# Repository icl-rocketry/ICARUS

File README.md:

# ICARUS
Imperial College london rocketry Attempts to be Resourceful by Using Solar power. A CanSat for the Mach-22 Competition

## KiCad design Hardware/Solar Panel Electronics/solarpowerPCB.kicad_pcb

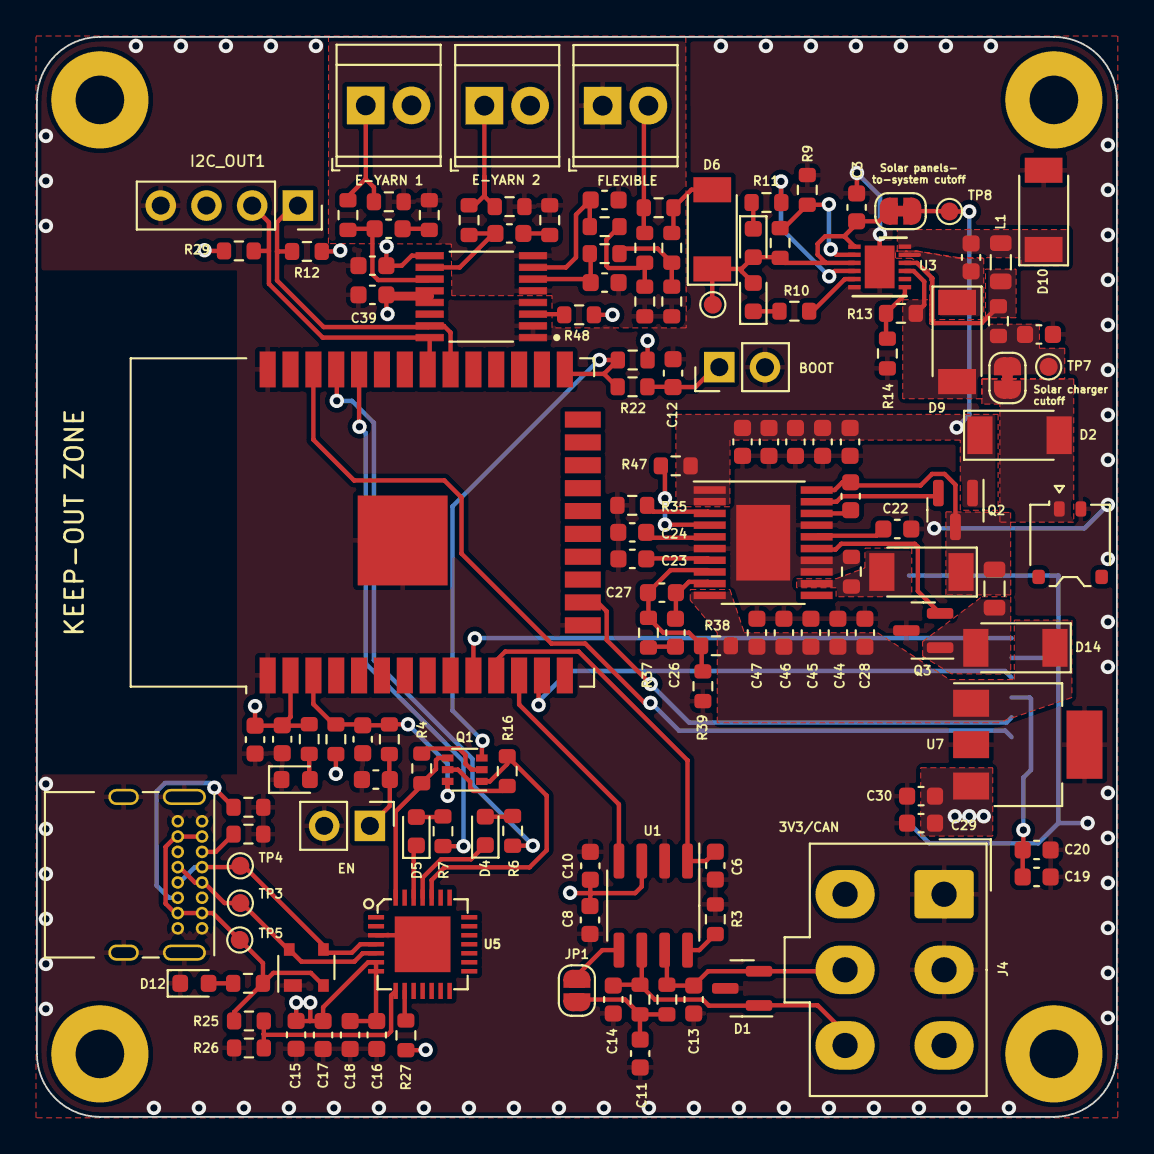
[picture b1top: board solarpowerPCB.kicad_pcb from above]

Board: 2 copper layers, 60.0 x 60.0 mm, 136 parts (1 on the bottom side), 80 nets.

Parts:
C1, C10, C20, C28, C29, C39: 10uF; C_0603_1608Metric
C2, C11, C12, C17, C18, C19, C38: 0.1uF; C_0603_1608Metric
C3, C5: 10u; C_0603_1608Metric
C4, C22: 1u; C_0603_1608Metric
C6: 160pF; C_0603_1608Metric
C7, C9: 1uF; C_0603_1608Metric
C8, C30: 100nF; C_0603_1608Metric
C13: 220pF; C_0603_1608Metric
C14: 220 pF; C_0603_1608Metric
C15: 47uF; C_0603_1608Metric
C16: 1.0uF; C_0603_1608Metric
C21, C40, C41, C42, C43: 2.2u; C_0603_1608Metric
C23, C25: 0.1u; C_0603_1608Metric
C24: 1.6n; C_0603_1608Metric
C26: 55nF; C_0603_1608Metric
C27: 0.01nF; C_0603_1608Metric
C31, C32: 10nF; C_0603_1608Metric
C33, C34: C_0603_1608Metric
C44, C45: 47u; C_0603_1608Metric
C46, C47: 0.47u; C_0603_1608Metric
D1: SM712_SOT23; SOT-23
D2, D10: CMSH3-20MA; D_SOD-128
D3, D4, D5: LED; LED_0603_1608Metric
D6: CMSH1-20MA; D_SOD-128
D7: FAULT LED; LED_0603_1608Metric
D8: CHRG LED; LED_0603_1608Metric
D9: D; D_SOD-128
D11: SP0503BAHT; SOT-143
D12: USB_LED; LED_0603_1608Metric
D13: D_Schottky_10V_1.5A; D_SOD-128
D14: D_Schottky_6V; D_SOD-128
I2C_OUT1: Conn_01x04_Female; PinSocket_1x04_P2.54mm_Vertical
J1: Screw_Terminal_SolarPanel_Input; TerminalBlock_TE_282834-2_1x02_P2.54mm_Horizontal
J3, J5: Conn_01x02_Male; PinHeader_1x02_P2.54mm_Vertical
J4: Conn_01x06_Male; Molex_Mini-Fit_Jr_5566-06A_2x03_P4.20mm_Vertical
J6: USB_C_Receptacle_USB2.0; USB_C_Receptacle_GCT_USB4085
J7: microSD_HC_Wuerth_693072010801
J13: Battery Connector; JST_ACH_BM02B-ACHSS-GAN-ETF_1x02-1MP_P1.20mm_Vertical
JP1: SolderJumper_2_Open; SolderJumper-2_P1.3mm_Open_RoundedPad1.0x1.5mm
JP2, JP3: SolderJumper_2_Bridged; SolderJumper-2_P1.3mm_Bridged_RoundedPad1.0x1.5mm
L1: 10u; L_0805_2012Metric
L2: 17uH; L_0805_2012Metric
Patch1, Patch2: TerminalBlock_TE_282834-2_1x02_P2.54mm_Horizontal
Q1: MMDT2222A; SOT-363_SC-70-6
Q2, Q3: Q_NMOS_DGS; SOT-23
R3, R10, R11, R48: 10k; R_0603_1608Metric
R4, R16, R17, R19: 10K; R_0603_1608Metric
R5, R6, R7, R28: 470; R_0603_1608Metric
R8: 340k; R_0603_1608Metric
R9: 100k; R_0603_1608Metric
R12, R27, R29: 4.7k; R_0603_1608Metric
R13: 560k; R_0603_1608Metric
R14: 450k; R_0603_1608Metric
R15: 0.05; R_0603_1608Metric
R18, R22: 0; R_0603_1608Metric
R20, R21: 60; R_0603_1608Metric
R23, R24: 5.1k; R_0603_1608Metric
R25: 24k; R_0603_1608Metric
R26: 47k; R_0603_1608Metric
R30, R33, R47: 1M; R_0603_1608Metric
R31, R34: 400k; R_0603_1608Metric
R32: 0.22-Current Sense; R_0603_1608Metric
R35: 18.3k; R_0603_1608Metric
R36: 15m; R_0603_1608Metric
R37: 17k; R_0603_1608Metric
R38: 1000; R_0603_1608Metric
R39: 332; R_0603_1608Metric
R40, R41, R42, R43, R44, R45: 1k; R_0603_1608Metric
R_Shunt1, R_Shunt2: 1k; R_0603_1608Metric
TP3, TP4, TP5: TestPoint; TestPoint_Pad_D1.0mm
TP6: TP_Vsolarpanel; TestPoint_Pad_D1.0mm
TP7: TP_BAT; TestPoint_Pad_D1.0mm
TP8: TP_Vout; TestPoint_Pad_D1.0mm
U1: SN65HVD230; SOIC-8_3.9x4.9mm_P1.27mm
U2: ESP32-WROOM-32D; ESP32-WROOM-32
U3: LT3652EDD; DFN-12-1EP_3x3mm_P0.45mm_EP1.66x2.38mm
U5: CP2102-GMR-QFN28; QFN28G_0.5-5X5MM
U6: LM5118MH; Texas_PWP0020A
U7: LT1963AxST-3.3; SOT-223-3_TabPin2
U9: ADS1219IPWT; SOP65P640X120-16N

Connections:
+3V3: C1.1, C2.1, C8.1, C10.1, C15.2, C16.2, C17.2, C18.2, C19.1, C20.1, C29.2, C30.2, C38.1, C39.2, I2C_OUT1.3, J4.3, J7.4 (VDD), R5.1, R12.1, R17.1, R19.1, R27.1, R29.1, R48.2, U1.3 (VCC), U2.2 (VDD), U5.6 (VDD), U5.7 (REGIN), U7.3 (OUT), U9.9 (REFP), U9.12 (AVDD), U9.13 (DVDD)
/ADC/AIN0N: C31.2, R41.2
/ADC/AIN0P: C31.1, R40.1, U9.11 (AIN0)
/ADC/AIN1N: C32.2, R43.2
/ADC/AIN1P: C32.1, R42.1, U9.10 (AIN1)
/ADC/AIN2P: C33.1, R44.1, U9.7 (AIN2)
/ADC/AIN3P: C34.1, R45.1, U9.6 (AIN3)
/BOOT: Q1.3 (C2), R19.2, R22.1, U2.25 (IO0)
/CAN_HIGH: C13.2, D1.2 (A2), J4.5, R20.1, U1.7 (CANH)
/CAN_LOW: C14.2, D1.1 (A1), J4.6, R21.2, U1.6 (CANL)
/CAN_RX: U1.4 (R), U2.12 (IO27)
/CAN_TX: C6.2, U1.1 (D), U2.11 (IO26)
/DTR: Q1.4 (E2), R4.2, U5.28 (DTR)
/EN: C7.1, Q1.6 (C1), R17.2, R18.1, U2.3 (EN)
/HSPI_MISO: J7.7 (DAT0), U2.10 (IO25)
/HSPI_MOSI: J7.3 (CMD), U2.16 (IO13)
/HSPI_SCLK: J7.5 (CLK), U2.13 (IO14)
/RTS: Q1.1 (E1), R16.2, U5.24 (RTS)
/RXD: D4.1 (K), U5.25 (RXD)
/SCL: I2C_OUT1.2, R29.2, U2.31 (IO19), U9.16 (SCL)
/SDA: I2C_OUT1.1, R12.2, U2.30 (IO18), U9.15 (SDA)
/Solar Charger/V_solarpanel: J1.2, R30.1, R32.1
/SolarPanelVoltage1: R30.2, R31.1, R44.2
/SolarPanelVoltage2: R33.2, R34.1, R45.2
/TXD: D5.1 (K), U5.26 (TXD)
/VSolCharger: C21.1, C40.1, C41.1, C42.1, C43.1, D2.1 (K), JP2.2 (B), Q2.1 (D), R47.1, TP8.1, U6.1 (VIN), U6.2 (UVLO)
/VoltageReg/V_reg: C28.2, C44.1, C45.1, C46.1, C47.1, D14.1 (K), R38.1, U6.10 (VOUT), U7.1 (IN)
/Vref: JP1.1 (A), U1.5 (Vref)
/usb_to_uart/Data+: D11.3 (K), J6.A6 (D+), J6.B6 (D+), TP4.1, U5.4 (D+)
/usb_to_uart/Data-: D11.4 (K), J6.A7 (D-), J6.B7 (D-), TP3.1, U5.5 (D-)
/~SD_CS: J7.2 (DAT3/CD), U2.36 (IO22)
GND: C1.2, C2.2, C3.1, C5.1, C6.1, C7.2, C8.2, C9.1, C10.2, C11.2, C12.1, C13.1, C14.1, C15.1, C16.1, C17.1, C18.1, C19.2, C20.2, C21.2, C22.2, C23.2, C24.2, C28.1, C29.1, C30.1, C38.2, C39.1, C40.2, C41.2, C42.2, C43.2, C44.2, C45.2, C46.2, C47.2, D1.3 (common), D3.1 (K), D10.2 (A), D11.1 (A), D12.1 (K), I2C_OUT1.4, J3.2, J4.1, J4.2, J5.2, J6.A1 (GND), J6.A12 (GND), J6.B1 (GND), J6.B12 (GND), J6.S1 (SHIELD), J7.6 (VSS), J7.9 (SHIELD), J13.2, Q3.3 (S), R3.2, R9.2, R14.2, R23.2, R24.1, R26.1, R35.2, R36.2, R39.2, U1.2 (GND), U2.1 (GND), U2.15 (GND), U2.38 (GND), U2.39 (GND), U3.6 (TIMER), U3.13 (GND), U5.3 (GND), U5.29 (GND@1), U6.6 (AGND), U6.13 (CSG), U6.14 (PGND), U6.17 (VCCX), U6.21 (EP), U7.2 (GND), U9.1 (A0), U9.2 (A1), U9.4 (DGND)
GNDA: C33.2, C34.2, J1.1, Patch1.2, Patch2.2, R31.2, R34.2, R41.1, R43.1, R_Shunt1.2, R_Shunt2.2, U9.5 (AGND), U9.8 (REFN)
unnamed: C3.2, D6.1 (K), D7.2 (A), D8.2 (A), JP2.1 (A), R8.1, TP6.1, U3.1 (VIN), U3.3 (~SHDN)
unnamed: C4.1, D9.1 (K), U3.11 (BOOST)
unnamed: C4.2, D10.1 (K), L1.1, U3.12 (SW)
unnamed: C5.2, D9.2 (A), JP3.1 (A), R13.1, R15.2, TP7.1, U3.9 (BAT)
unnamed: C9.2, J3.1, R18.2
unnamed: C11.1, JP1.2 (B), R20.2, R21.1
unnamed: C12.2, J5.1, R22.2
unnamed: C22.1, U6.16 (VCC)
unnamed: C23.1, U6.7 (SS)
unnamed: C24.1, U6.5 (RAMP)
unnamed: C25.1, U6.18 (HB)
unnamed: C25.2, D13.1 (K), L2.1, Q2.3 (S), U6.20 (HS)
unnamed: C26.1, R37.1
unnamed: C26.2, C27.2, U6.9 (COMP)
unnamed: C27.1, R37.2, R38.2, R39.1, U6.8 (FB)
unnamed: D2.2 (A), J13.1, JP3.2 (B)
unnamed: D3.2 (A), R5.2
unnamed: D4.2 (A), R6.2
unnamed: D5.2 (A), R7.2
unnamed: D6.2 (A), R32.2, R33.1
unnamed: D7.1 (K), R10.1
unnamed: D8.1 (K), R11.1
unnamed: D12.2 (A), R28.2
unnamed: D13.2 (A), R36.1, U6.12 (CS)
unnamed: D14.2 (A), L2.2, Q3.1 (D)
unnamed: J6.A5 (CC1), R23.1
unnamed: J6.B5 (CC2), R24.2
unnamed: L1.2, R15.1, U3.10 (SENSE)
unnamed: Patch1.1, R40.2, R_Shunt1.1
unnamed: Patch2.1, R42.2, R_Shunt2.1
unnamed: Q1.2 (B1), R4.1
unnamed: Q1.5 (B2), R16.1
unnamed: Q2.2 (G), U6.19 (HO)
unnamed: Q3.2 (G), U6.15 (LO)
unnamed: R3.1, U1.8 (Rs)
unnamed: R6.1, U2.35 (TXD0/IO1)
unnamed: R7.1, U2.34 (RXD0/IO3)
unnamed: R8.2, R9.1, U3.2 (VIN_REG)
unnamed: R10.2, U3.5 (~FAULT)
unnamed: R11.2, U3.4 (~CHRG)
unnamed: R13.2, R14.1, U3.7 (VFB)
unnamed: R25.1, R26.2, U5.8 (VBUS)
unnamed: R27.2, U5.9 (~RST)
unnamed: R35.1, U6.3 (RT)
unnamed: R47.2, U6.4 (EN)
unnamed: R48.1, U9.3 (~RESET)
VBUS: D11.2 (K), J6.A4 (VBUS), J6.A9 (VBUS), J6.B4 (VBUS), J6.B9 (VBUS), R25.2, R28.1, TP5.1

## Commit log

2022-04-02 Add .gitignore
2022-04-02 Added some basic components including LT3652 solar charger
2022-04-04 Changed files to KiCAD 6.0
2022-04-04 Move uart to separate sheet and fix
2022-04-04 Add RICARDO bus and CAN
2022-04-04 Change MCU to PICO-D4
2022-04-04 Add SD card
2022-04-05 Remove extra pdf file
2022-04-06 Edited the charging circuit, need to resize components
2022-04-07 Components sized for our requirements. Added ideal diode IC LTC4411 which is more efficient than a normal diode.
2022-04-07 Added voltage regulator from Pick Rick
2022-04-07 Connectvoltage regulator and solar panel charger
2022-04-07 Add i2c breakout
2022-04-08 Add ADC for solar yarn patch
2022-04-08 Made changes to solar charging circuit
2022-04-08 Added power measuring circuitry using potential dividers. Needs to be double checked
2022-04-08 Added voltage regulators. Need to size components
2022-04-09 Changed to use ADS131M04 adc instead of esp32 adc for power calculation
2022-04-09 Assigned Footprints (preliminary - just to do a quick layout)
2022-04-09 Add Antenna
2022-04-10 Started pcb layout
2022-04-10 started pcb layout(2)
2022-04-10 PCB layout
2022-04-10 quick layout change
2022-04-10 Preliminary Layout done. (46x77mm)
2022-04-10 Fix edge cuts
2022-04-10 Fix dielectric thicknesses
2022-05-17 Layed out parts a bit more
2022-05-20 Sized the buck-boost converter components. Need to complete pcb layout.
2022-05-21 Fixed an error in sizing of feedback resistors and capacitors
2022-05-24 Need to do routing.
2022-05-24 New Layout (did not change subsystem layout)
2022-05-28 FIrmware started
2022-05-31 Partly done routing. Need to replace solar charging circuit
2022-06-03 Added another ADS component. Layout and routing can be continued.
2022-06-04 Top half routing done
2022-06-05 majority of routing done
2022-06-06 routing clean up
2022-06-07 Almost finished routing
2022-06-09 PCB done. Just needs checking
2022-06-09 LAra V3
    Barebones Structure *compiles*
2022-06-09 LAra V2
2022-06-09 LAra V1
2022-06-11 LAraV4
2022-06-14 LAra V5
    Added Sensor Library added unified sensor
2022-06-14 LAra V5
    Added DHT11 Library
2022-06-14 LAra V6
    GPS done and compiled
2022-06-14 LAra v7
2022-06-16 LAra V8
    Added pin definitions for actual board
2022-06-16 LAra V9
    Changed code to be a bit more clear
2022-06-16 LAra V10
2022-06-16 LAra V11
    *Compiles*
2022-06-18 LAraV12
2022-06-20 LoRa added to LAra
2022-06-22 LAra V14
2022-06-22 LAra V15
    delay added
2022-06-22 Remove librnp
2022-06-22 Re-added librnp
2022-06-23 compiles with Librnp lora
2022-06-23 MAch trying
2022-06-23 Modify buzzer behaviour
2022-06-23 LAra is back
2022-06-23 Initialise the routing table correctly
2022-06-23 Rearrange telemetry packet
2022-06-24 fixed errors with networkmanager usage. Implemented CommandHandler and added it to main application state. Good luck fellas!
2022-06-24 Continue getting code working
2022-06-24 Made changes
2022-06-24 ya boi fixed some stuff
2022-06-24 did stuff
2022-06-24 Add kiran changes
2022-06-24 maybe fixed
2022-06-24 fixed
2022-06-25 final code
2022-07-15 ICARUS v2
2022-07-15 removed can resistors
2022-07-18 removed ltc4411 on solar charger, added solder jumpers
2022-07-18 Just cleaning up
2022-07-20 final?
2022-07-29 Moved net from GPIO12
2022-08-08 attempt to fix vreg and charger
2022-09-12 ICARUS V2
    only ads and sd
